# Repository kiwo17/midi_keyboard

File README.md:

# Midi Keypad
building a mini portable keypad

My Interest have always been diverse, but music and electronics are the ones I constantly find myself drawn back to. With this project I am connecting both, by merging the 
creative and expressive qualities of music with the physical and technical structure of electronics. 

## Progress

### Schematic

Because I didn't want to use Bourns potentiometer sliders in my keypad I needed to replace them with a different component. 
I decided to add another encoder because I find them visually pleasing. Initially I wanted to use three encoders, but due to a shortage of GPIOs pins that wans't possible. 

I also had to adjust the connections between the different components and the ESP32 to make PCB routing easier

### Design

### Next steps ... 

  - firmware
  - assemble it

## BOM

| Item | Qty | Supplier | Cost/item | Total Cost | Link |
|---|---:|---|---:|---:|---|
| Key Caps (Encoders) | 2 | Aliexpres | $1.84 | $1.84 | [Link](https://de.aliexpress.com/item/4000326517211.html) |
| ESP32-S3-Zero | 1 | aliexpress | $5.62 | $5.62 | [Link](https://de.aliexpress.com/item/1005012733231291.html) |
| key switches | 3 | Aliexpress | $3.51 | $3.51 | [Link](https://de.aliexpress.com/item/1005013073233639.html) |
| The PCB | 1 | JLCPCB | $5.30 | $5.30 | [Link](https://www.jlcpbc.com) |
| EC11 | 2 | aliexpress | $3.31 | $3.31 | [Link](https://de.aliexpress.com/item/4000326517211.html) |
| Estimated total shipping | 1 | | | $23.40 | |

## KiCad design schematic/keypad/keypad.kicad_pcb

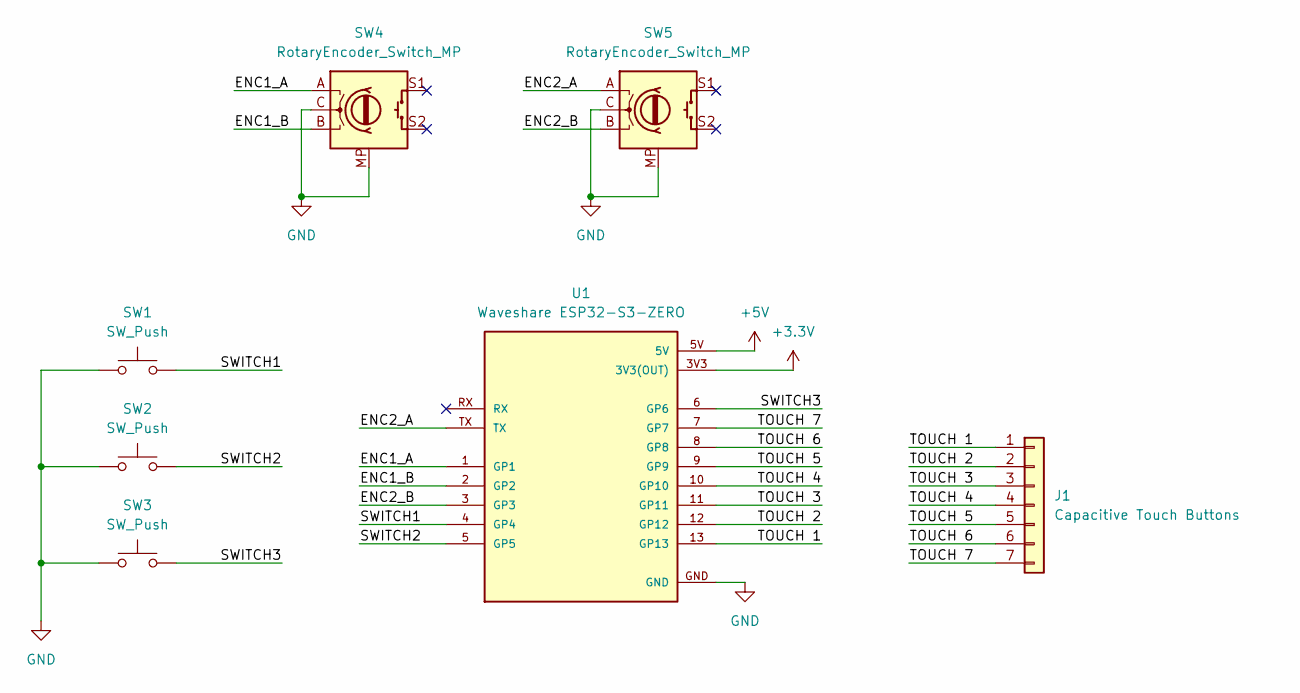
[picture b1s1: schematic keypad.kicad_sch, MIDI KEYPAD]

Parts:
J1: Capacitive Touch Buttons; Capacitive Keys
SW1, SW2, SW3: SW_Push; Kailh Choc Low-Profile Switches
SW4, SW5: RotaryEncoder_Switch_MP; RotaryEncoder_Alps_EC11E-Switch_Vertical_H20mm
U1: Waveshare ESP32-S3-ZERO; Waveshare ESP32-S3-Zero; PARTREV NA

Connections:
+3.3V: U1.3V3 (3V3(OUT))
+5V: U1.5V
/ENC1_A: SW4.A, U1.1 (GP1)
/ENC1_B: SW4.B, U1.2 (GP2)
/ENC2_A: SW5.A, U1.TX
/ENC2_B: SW5.B, U1.3 (GP3)
/SWITCH1: SW1.2, U1.4 (GP4)
/SWITCH2: SW2.2, U1.5 (GP5)
/SWITCH3: SW3.2, U1.6 (GP6)
/TOUCH 1: J1.1, U1.13 (GP13)
/TOUCH 2: J1.2, U1.12 (GP12)
/TOUCH 3: J1.3, U1.11 (GP11)
/TOUCH 4: J1.4, U1.10 (GP10)
/TOUCH 5: J1.5, U1.9 (GP9)
/TOUCH 6: J1.6, U1.8 (GP8)
/TOUCH 7: J1.7, U1.7 (GP7)
GND: SW1.1, SW2.1, SW3.1, SW4.C, SW4.MP, SW5.C, SW5.MP, U1.GND

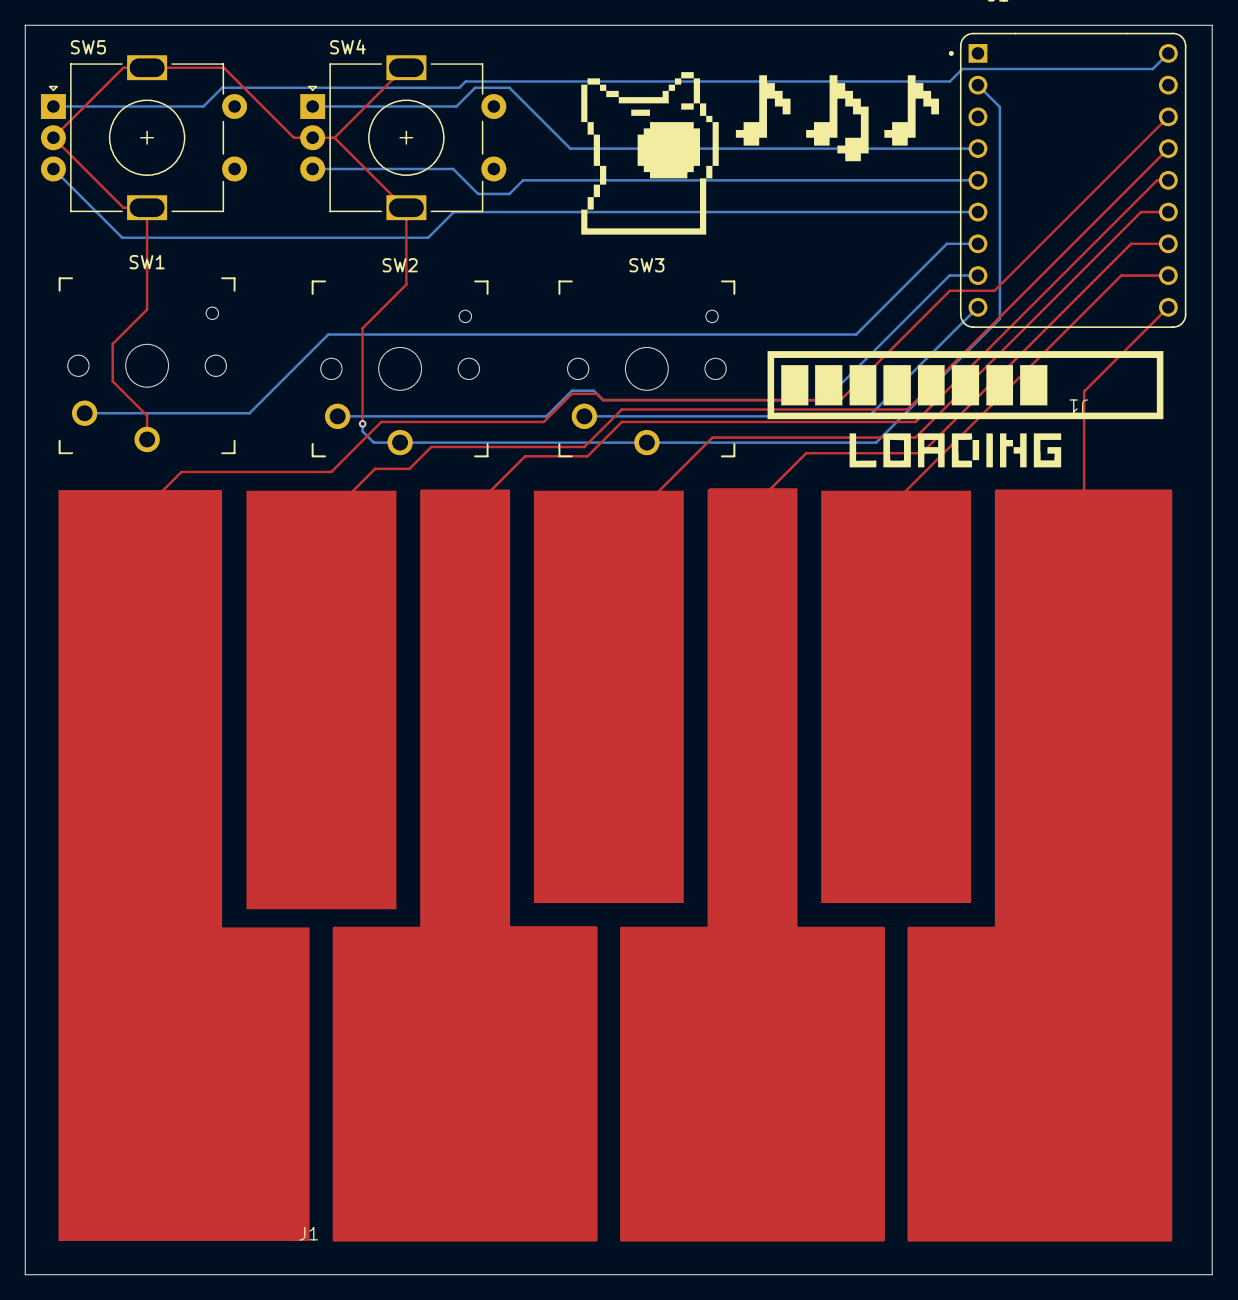
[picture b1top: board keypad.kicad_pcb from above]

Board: 2 copper layers, 95.0 x 100.0 mm, 7 parts (0 on the bottom side), 15 nets.

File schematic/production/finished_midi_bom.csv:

Designator,Footprint,Quantity,Value,LCSC Part #
J1,Capacitive Keys,1,Capacitive Touch Buttons,
"SW1, SW2, SW3",Kailh Choc Low-Profile Switches,3,SW_Push,
"SW4, SW5",RotaryEncoder_Alps_EC11E-Switch_Vertical_H20mm,2,RotaryEncoder_Switch_MP,
U1,Waveshare ESP32-S3-Zero,1,Waveshare ESP32-S3-ZERO,
